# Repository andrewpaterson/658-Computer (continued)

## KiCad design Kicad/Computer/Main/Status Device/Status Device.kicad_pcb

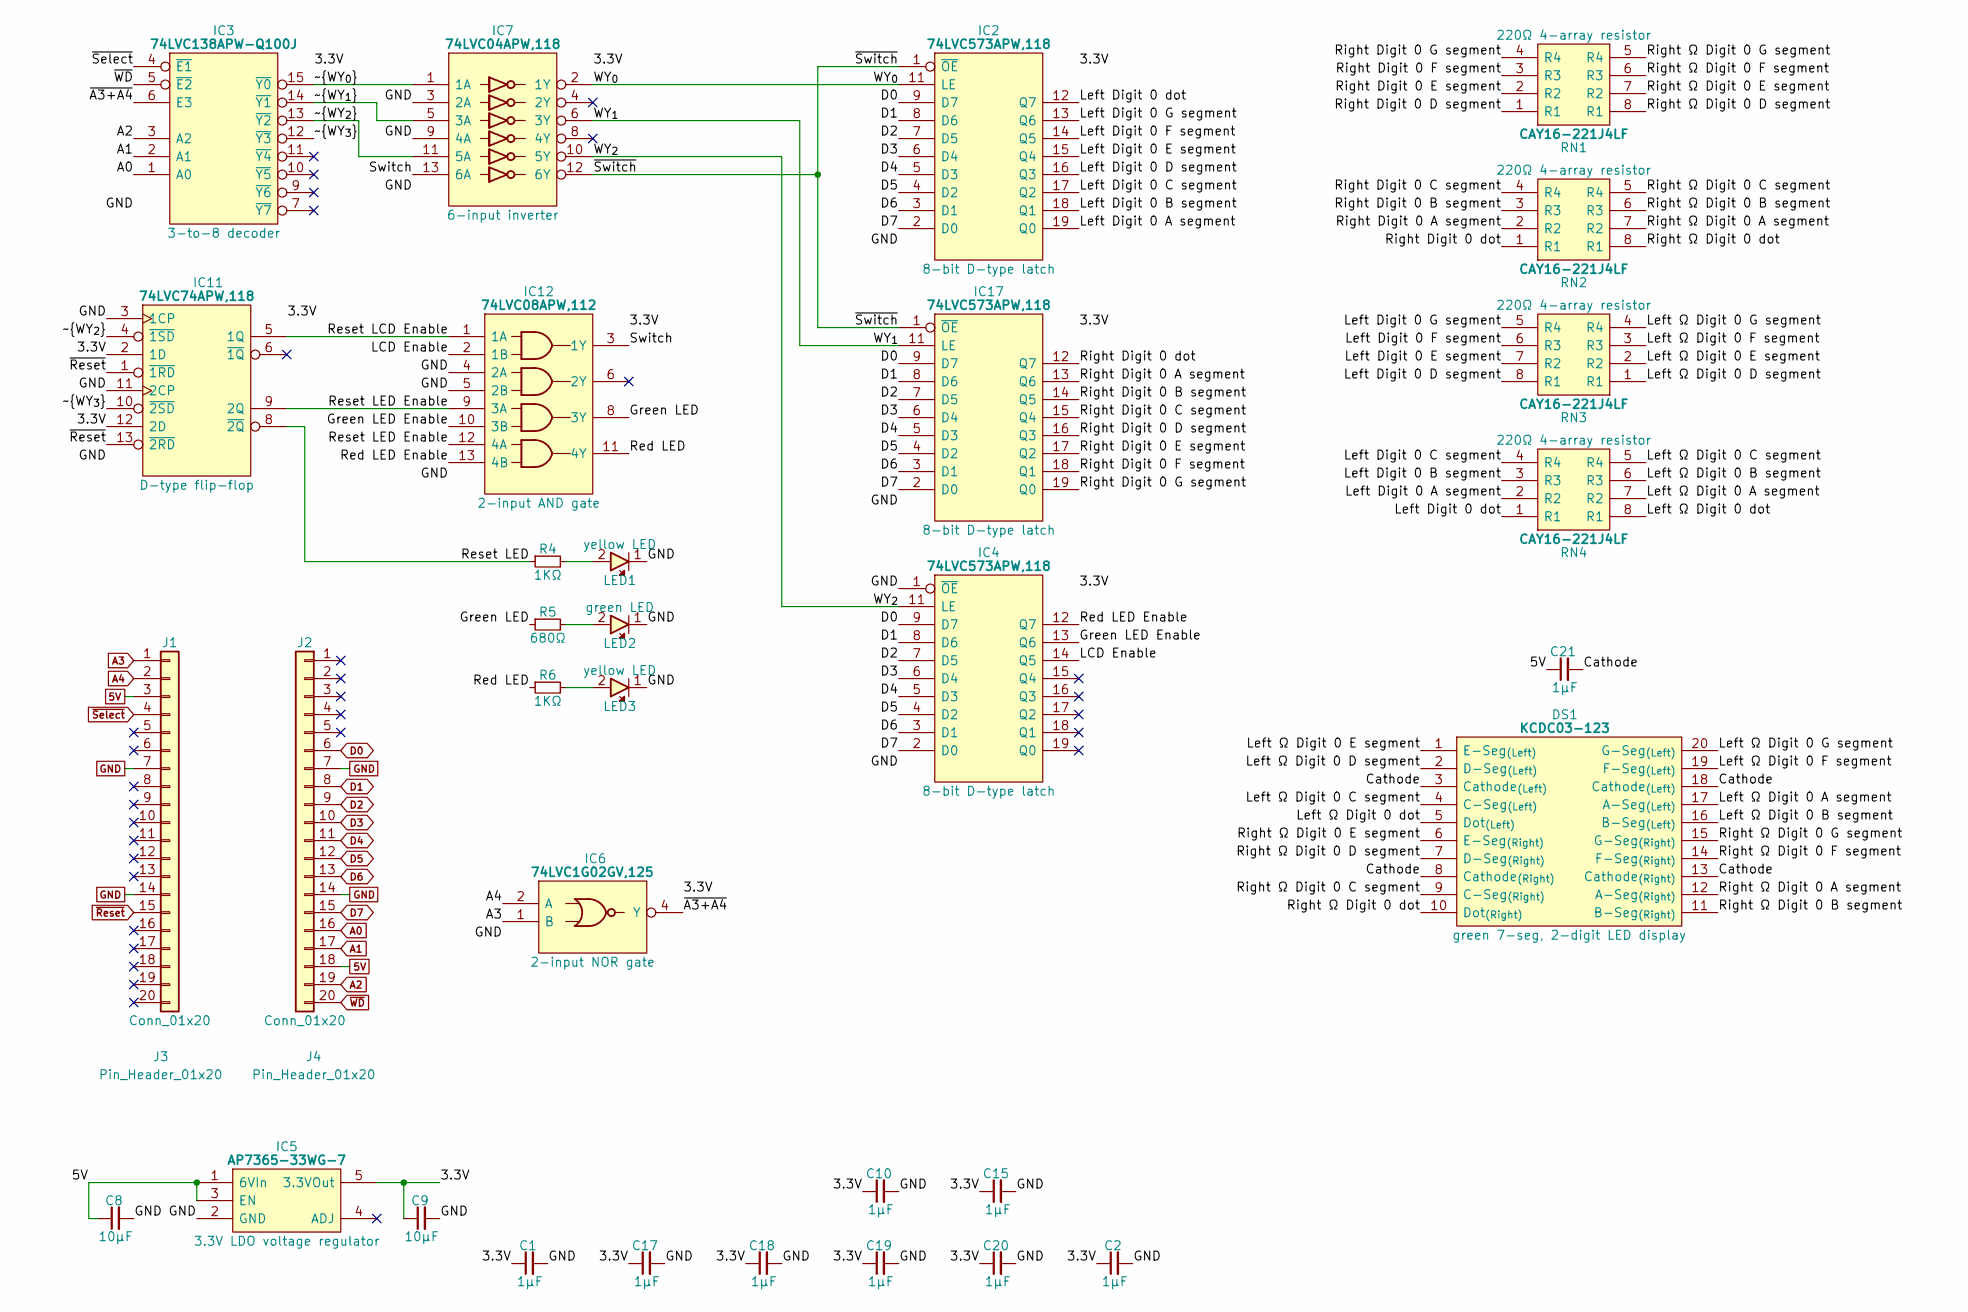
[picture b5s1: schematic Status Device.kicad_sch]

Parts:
C1, C2, C10, C15, C17, C18, C19, C20: 1μF; C_0805
C8, C9: 10µF; C_0805
C21: 1µF; C_0805
DS1: KCDC03-123; KCDC03123; Manufacturer_Part_Number KCDC03-123; Mouser Part Number N/A
IC2, IC4, IC17: 74LVC573APW,118; SOP65P640X110-20N; Mouser Part Number 771-74LVC573APW-T
IC3: 74LVC138APW-Q100J; SOP65P640X110-16N; Mouser Part Number 771-74LVC138APWQ100J
IC5: AP7365-33WG-7; SOT95P285X130-5N; Manufacturer_Part_Number AP7365-33WG-7; Mouser Part Number 621-AP7365-33WG-7
IC6: 74LVC1G02GV,125; SOT95P275X110-5N; Manufacturer_Part_Number 74LVC1G02GV,125; Mouser Part Number 771-LVC1G02GV125
IC7: 74LVC04APW,118; SOP65P640X110-14N; Manufacturer_Part_Number 74LVC04APW,118; Mouser Part Number 771-74LVC04APW-T
IC11: 74LVC74APW,118; SOP65P640X110-14N; Mouser Part Number 771-74LVC74APW-T
IC12: 74LVC08APW,112; SOP65P640X110-14N; Manufacturer_Part_Number 74LVC08APW,112; Mouser Part Number 771-74LVC08APW
J1, J2: Conn_01x20; SIP_20_Pins
J3, J4: Pin_Header_01x20; PinHeader_1x20_P2.54mm_Vertical
LED1, LED3: 150224YS73100A; 150224BS73100A
LED2: 150224VS73100A; Manufacturer_Part_Number 150224VS73100A; Mouser Part Number 710-150224VS73100A
R4, R6: 1KΩ; R_0805
R5: 680Ω; R_0805
RN1, RN2, RN3, RN4: CAY16-221J4LF; CAY16-F4; Manufacturer_Part_Number CAY16-221J4LF; Mouser Part Number 652-CAY16-221J4LF

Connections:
5V: C8.1, C21.1, IC5.1 (6VIn), IC5.3 (EN), J1.3, J2.18
/3.3V: C1.1, C2.1, C9.1, C10.1, C15.1, C17.1, C18.1, C19.1, C20.1, IC2.20 (3V), IC3.16 (3V), IC4.20 (3V), IC5.5 (3.3VOut), IC6.5 (3V), IC7.14 (3V), IC11.2 (1D), IC11.12 (2D), IC11.14 (3V), IC12.14 (3V), IC17.20 (3V)
/Cathode: C21.2, DS1.3 (Cathode_{(Left)}), DS1.8 (Cathode_{(Right)}), DS1.13 (Cathode_{(Right)}), DS1.18 (Cathode_{(Left)})
/Green LED: IC12.8 (3Y), R5.1
/Green LED Enable: IC4.13 (Q6), IC12.10 (3B)
/LCD Enable: IC4.14 (Q5), IC12.2 (1B)
/Left Digit 0 A segment: IC2.19 (Q0), RN4.2 (R2)
/Left Digit 0 B segment: IC2.18 (Q1), RN4.3 (R3)
/Left Digit 0 C segment: IC2.17 (Q2), RN4.4 (R4)
/Left Digit 0 D segment: IC2.16 (Q3), RN3.8 (R1)
/Left Digit 0 E segment: IC2.15 (Q4), RN3.7 (R2)
/Left Digit 0 F segment: IC2.14 (Q5), RN3.6 (R3)
/Left Digit 0 G segment: IC2.13 (Q6), RN3.5 (R4)
/Left Digit 0 dot: IC2.12 (Q7), RN4.1 (R1)
/Left Ω Digit 0 A segment: DS1.17 (A-Seg_{(Left)}), RN4.7 (R2)
/Left Ω Digit 0 B segment: DS1.16 (B-Seg_{(Left)}), RN4.6 (R3)
/Left Ω Digit 0 C segment: DS1.4 (C-Seg_{(Left)}), RN4.5 (R4)
/Left Ω Digit 0 D segment: DS1.2 (D-Seg_{(Left)}), RN3.1 (R1)
/Left Ω Digit 0 E segment: DS1.1 (E-Seg_{(Left)}), RN3.2 (R2)
/Left Ω Digit 0 F segment: DS1.19 (F-Seg_{(Left)}), RN3.3 (R3)
/Left Ω Digit 0 G segment: DS1.20 (G-Seg_{(Left)}), RN3.4 (R4)
/Left Ω Digit 0 dot: DS1.5 (Dot_{(Left)}), RN4.8 (R1)
/Red LED: IC12.11 (4Y), R6.1
/Red LED Enable: IC4.12 (Q7), IC12.13 (4B)
/Reset LCD Enable: IC11.5 (1Q), IC12.1 (1A)
/Reset LED: IC11.8 (~2Q), R4.1
/Reset LED Enable: IC11.9 (2Q), IC12.9 (3A), IC12.12 (4A)
/Right Digit 0 A segment: IC17.13 (Q6), RN2.2 (R2)
/Right Digit 0 B segment: IC17.14 (Q5), RN2.3 (R3)
/Right Digit 0 C segment: IC17.15 (Q4), RN2.4 (R4)
/Right Digit 0 D segment: IC17.16 (Q3), RN1.1 (R1)
/Right Digit 0 E segment: IC17.17 (Q2), RN1.2 (R2)
/Right Digit 0 F segment: IC17.18 (Q1), RN1.3 (R3)
/Right Digit 0 G segment: IC17.19 (Q0), RN1.4 (R4)
/Right Digit 0 dot: IC17.12 (Q7), RN2.1 (R1)
/Right Ω Digit 0 A segment: DS1.12 (A-Seg_{(Right)}), RN2.7 (R2)
/Right Ω Digit 0 B segment: DS1.11 (B-Seg_{(Right)}), RN2.6 (R3)
/Right Ω Digit 0 C segment: DS1.9 (C-Seg_{(Right)}), RN2.5 (R4)
/Right Ω Digit 0 D segment: DS1.7 (D-Seg_{(Right)}), RN1.8 (R1)
/Right Ω Digit 0 E segment: DS1.6 (E-Seg_{(Right)}), RN1.7 (R2)
/Right Ω Digit 0 F segment: DS1.14 (F-Seg_{(Right)}), RN1.6 (R3)
/Right Ω Digit 0 G segment: DS1.15 (G-Seg_{(Right)}), RN1.5 (R4)
/Right Ω Digit 0 dot: DS1.10 (Dot_{(Right)}), RN2.8 (R1)
/Switch: IC7.13 (6A), IC12.3 (1Y)
/WY_{0}: IC2.11 (LE), IC7.2 (1Y)
/WY_{1}: IC7.6 (3Y), IC17.11 (LE)
/WY_{2}: IC4.11 (LE), IC7.10 (5Y)
/~A3+A4: IC3.6 (E3), IC6.4 (Y)
/~Switch: IC2.1 (~OE), IC7.12 (6Y), IC17.1 (~OE)
/~WY_{0}: IC3.15 (~Y0), IC7.1 (1A)
/~WY_{1}: IC3.14 (~Y1), IC7.5 (3A)
/~WY_{2}: IC3.13 (~Y2), IC7.11 (5A), IC11.4 (~1SD)
/~WY_{3}: IC3.12 (~Y3), IC11.10 (~2SD)
A0: IC3.1 (A0), J2.16
A1: IC3.2 (A1), J2.17
A2: IC3.3 (A2), J2.19
A3: IC6.1 (B), J1.1
A4: IC6.2 (A), J1.2
D0: IC2.9 (D7), IC4.9 (D7), IC17.9 (D7), J2.6
D1: IC2.8 (D6), IC4.8 (D6), IC17.8 (D6), J2.8
D2: IC2.7 (D5), IC4.7 (D5), IC17.7 (D5), J2.9
D3: IC2.6 (D4), IC4.6 (D4), IC17.6 (D4), J2.10
D4: IC2.5 (D3), IC4.5 (D3), IC17.5 (D3), J2.11
D5: IC2.4 (D2), IC4.4 (D2), IC17.4 (D2), J2.12
D6: IC2.3 (D1), IC4.3 (D1), IC17.3 (D1), J2.13
D7: IC2.2 (D0), IC4.2 (D0), IC17.2 (D0), J2.15
GND: C1.2, C2.2, C8.2, C9.2, C10.2, C15.2, C17.2, C18.2, C19.2, C20.2, IC2.10 (GND), IC3.8 (GND), IC4.1 (~OE), IC4.10 (GND), IC5.2 (GND), IC6.3 (GND), IC7.3 (2A), IC7.7 (GND), IC7.9 (4A), IC11.3 (1CP), IC11.7 (GND), IC11.11 (2CP), IC12.4 (2A), IC12.5 (2B), IC12.7 (GND), IC17.10 (GND), J1.7, J1.14, J2.7, J2.14, LED1.1, LED2.1, LED3.1
unnamed: LED1.2, R4.2
unnamed: LED2.2, R5.2
unnamed: LED3.2, R6.2
~Reset: IC11.1 (~1RD), IC11.13 (~2RD), J1.15
~Select: IC3.4 (~E1), J1.4
~WD: IC3.5 (~E2), J2.20

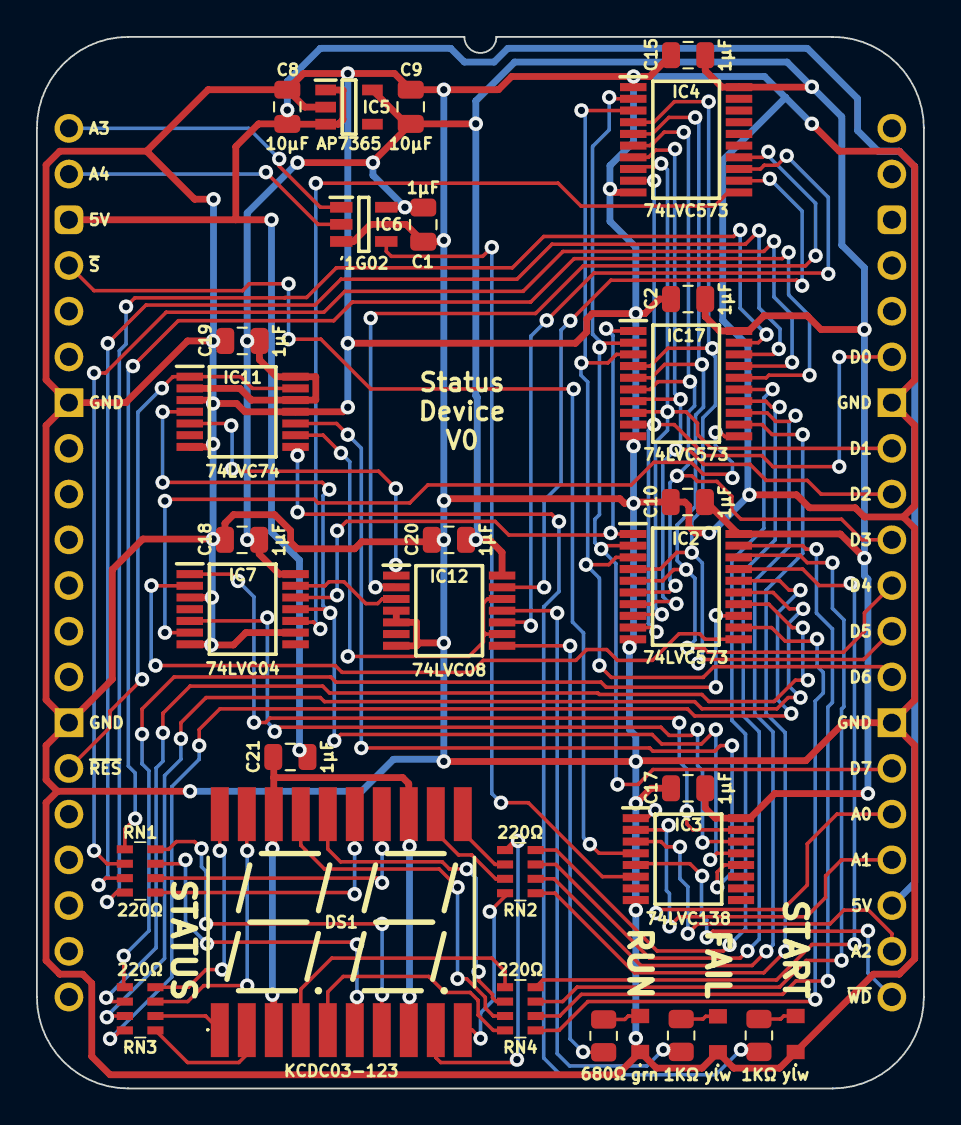
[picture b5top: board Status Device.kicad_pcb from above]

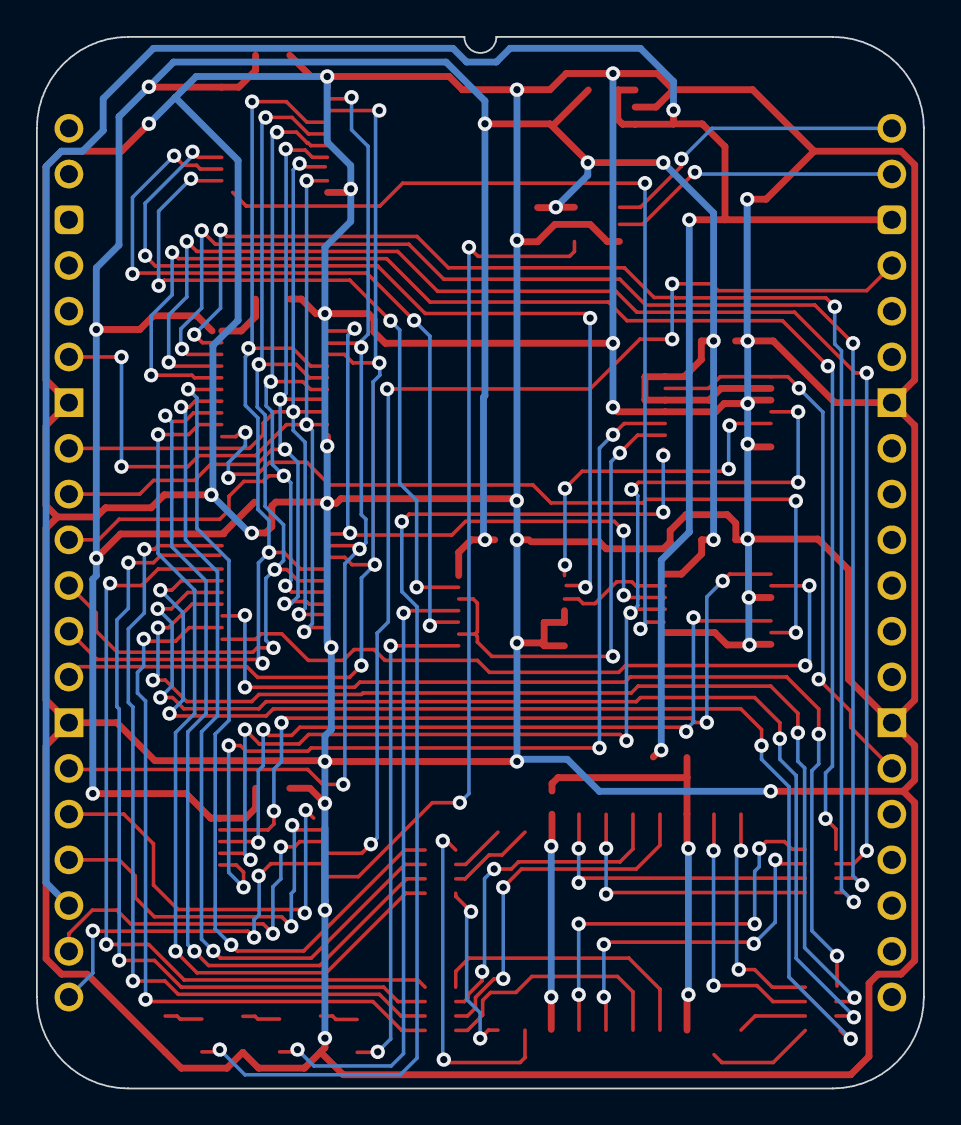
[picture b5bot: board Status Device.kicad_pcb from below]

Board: 2 copper layers, 49.3 x 58.4 mm, 35 parts (2 on the bottom side), 73 nets.

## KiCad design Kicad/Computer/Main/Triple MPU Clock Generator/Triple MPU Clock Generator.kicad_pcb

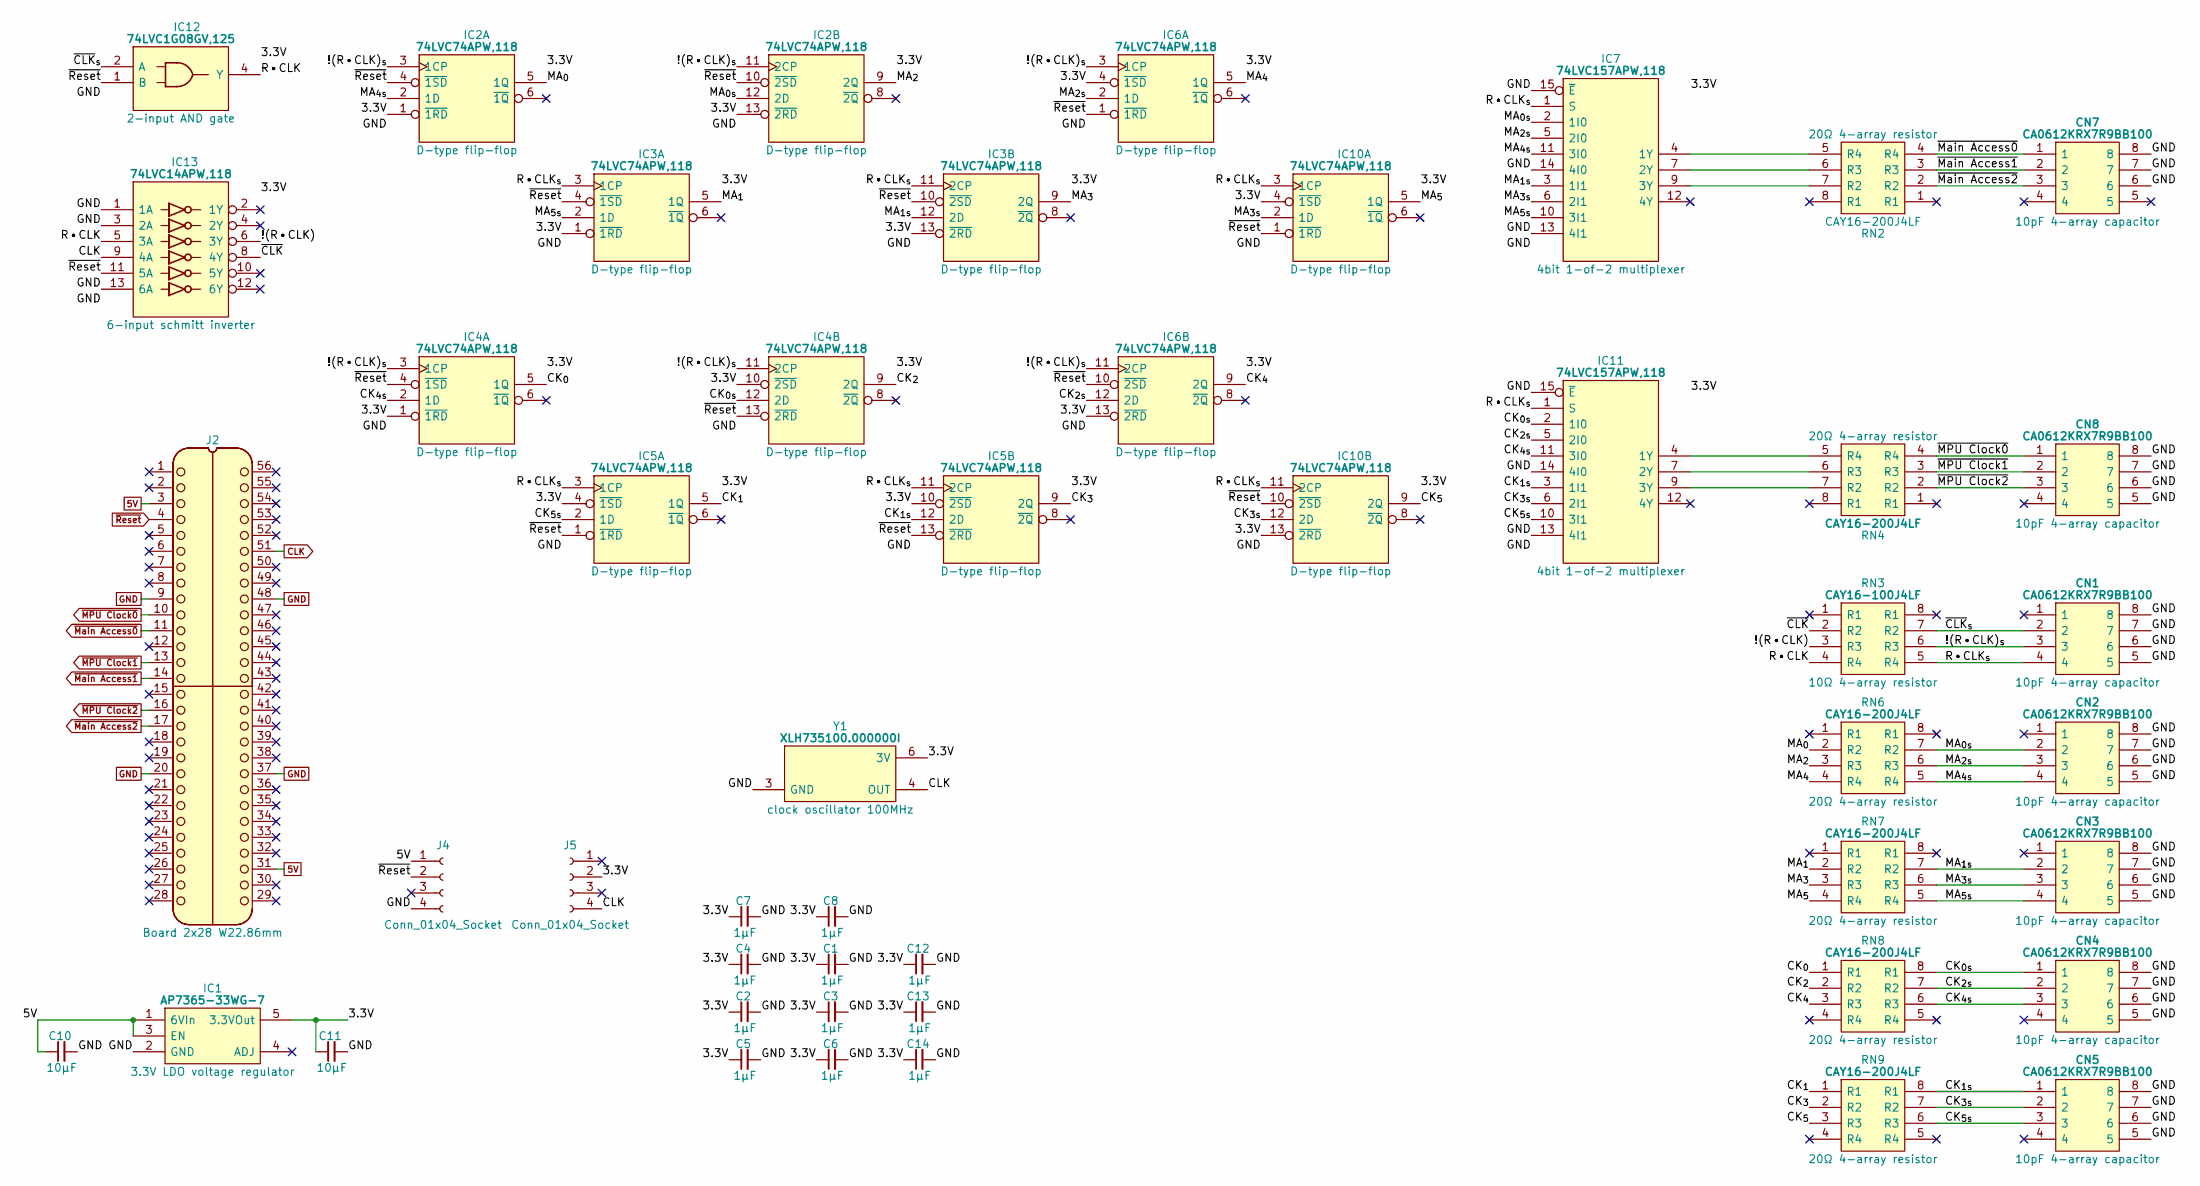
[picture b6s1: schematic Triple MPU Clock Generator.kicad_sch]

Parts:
C1, C2, C3, C4, C5, C6, C7, C8, C12, C13, C14: 1μF; C_0805
C10, C11: 10µF; C_0805
CN1, CN2, CN3, CN4, CN5, CN7, CN8: CA0612KRX7R9BB100; Manufacturer_Part_Number CA0612KRX7R9BB102; Mouser Part Number 603-CA612KRX7R9BB102
IC1: AP7365-33WG-7; SOT95P285X130-5N; Manufacturer_Part_Number AP7365-33WG-7; Mouser Part Number 621-AP7365-33WG-7
IC2, IC3, IC4, IC5, IC6, IC10: 74LVC74APW,118; SOP65P640X110-14N; Mouser Part Number 771-74LVC74APW-T
IC7, IC11: 74LVC157APW,118; SOP65P640X110-16N; Mouser Part Number 771-74LVC157APW-T
IC12: 74LVC1G08GV,125; SOT95P275X110-5N; Manufacturer_Part_Number 74LVC1G08GV,125; Mouser Part Number 771-74LVC1G08GV
IC13: 74LVC14APW,118; SOP65P640X110-14N; Manufacturer_Part_Number 74LVC14APW,118; Mouser Part Number 771-74LVC14APW-T
J2: Board 2x28 W22.86mm; DIP-56_Board_W22.86mm
J4, J5: Conn_01x04_Socket; PinSocket_1x04_P2.54mm_Vertical
RN2, RN4, RN6, RN7, RN8, RN9: CAY16-200J4LF; CAY16-F4; Manufacturer_Part_Number CAY16-331J4LF; Mouser Part Number 652-CAY16-331J4LF
RN3: CAY16-100J4LF; CAY16-F4; Manufacturer_Part_Number CAY16-331J4LF; Mouser Part Number 652-CAY16-331J4LF
Y1: XLH735100.000000I; XLH735100000000I; Mouser Part Number 972-XLH735100000000I

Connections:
5V: C10.1, IC1.1 (6VIn), IC1.3 (EN), J2.3, J2.31, J4.1
/3.3V: C1.1, C2.1, C3.1, C4.1, C5.1, C6.1, C7.1, C8.1, C11.1, C12.1, C13.1, C14.1, IC1.5 (3.3VOut), IC2.1 (~1RD), IC2.13 (~2RD), IC2.14 (3V), IC3.1 (~1RD), IC3.13 (~2RD), IC3.14 (3V), IC4.1 (~1RD), IC4.10 (~2SD), IC4.14 (3V), IC5.4 (~1SD), IC5.10 (~2SD), IC5.14 (3V), IC6.4 (~1SD), IC6.13 (~2RD), IC6.14 (3V), IC7.16 (3V), IC10.4 (~1SD), IC10.13 (~2RD), IC10.14 (3V), IC11.16 (3V), IC12.5 (3V), IC13.14 (3V), J5.2, Y1.6 (3V); also elsewhere on the board
/!(R•CLK): IC13.6 (3Y), RN3.3 (R3)
/!(R•CLK)_{s}: CN1.3, IC2.3 (1CP), IC2.11 (2CP), IC4.3 (1CP), IC4.11 (2CP), IC6.3 (1CP), IC6.11 (2CP), RN3.6 (R3)
/CK_{0s}: CN4.1, IC4.12 (2D), IC11.2 (1I0), RN8.8 (R1)
/CK_{0}: IC4.5 (1Q), RN8.1 (R1)
/CK_{1s}: CN5.1, IC5.12 (2D), IC11.3 (1I1), RN9.8 (R1)
/CK_{1}: IC5.5 (1Q), RN9.1 (R1)
/CK_{2s}: CN4.2, IC6.12 (2D), IC11.5 (2I0), RN8.7 (R2)
/CK_{2}: IC4.9 (2Q), RN8.2 (R2)
/CK_{3s}: CN5.2, IC10.12 (2D), IC11.6 (2I1), RN9.7 (R2)
/CK_{3}: IC5.9 (2Q), RN9.2 (R2)
/CK_{4s}: CN4.3, IC4.2 (1D), IC11.11 (3I0), RN8.6 (R3)
/CK_{4}: IC6.9 (2Q), RN8.3 (R3)
/CK_{5s}: CN5.3, IC5.2 (1D), IC11.10 (3I1), RN9.6 (R3)
/CK_{5}: IC10.9 (2Q), RN9.3 (R3)
/MA_{0s}: CN2.2, IC2.12 (2D), IC7.2 (1I0), RN6.7 (R2)
/MA_{0}: IC2.5 (1Q), RN6.2 (R2)
/MA_{1s}: CN3.2, IC3.12 (2D), IC7.3 (1I1), RN7.7 (R2)
/MA_{1}: IC3.5 (1Q), RN7.2 (R2)
/MA_{2s}: CN2.3, IC6.2 (1D), IC7.5 (2I0), RN6.6 (R3)
/MA_{2}: IC2.9 (2Q), RN6.3 (R3)
/MA_{3s}: CN3.3, IC7.6 (2I1), IC10.2 (1D), RN7.6 (R3)
/MA_{3}: IC3.9 (2Q), RN7.3 (R3)
/MA_{4s}: CN2.4, IC2.2 (1D), IC7.11 (3I0), RN6.5 (R4)
/MA_{4}: IC6.5 (1Q), RN6.4 (R4)
/MA_{5s}: CN3.4, IC3.2 (1D), IC7.10 (3I1), RN7.5 (R4)
/MA_{5}: IC10.5 (1Q), RN7.4 (R4)
/R•CLK: IC12.4 (Y), IC13.5 (3A), RN3.4 (R4)
/R•CLK_{s}: CN1.4, IC3.3 (1CP), IC3.11 (2CP), IC5.3 (1CP), IC5.11 (2CP), IC7.1 (S), IC10.3 (1CP), IC10.11 (2CP), IC11.1 (S), RN3.5 (R4)
/~CLK: IC13.8 (4Y), RN3.2 (R2)
/~CLK_{s}: CN1.2, IC12.2 (A), RN3.7 (R2)
CLK: IC13.9 (4A), J2.51, J5.4, Y1.4 (OUT)
GND: C1.2, C2.2, C3.2, C4.2, C5.2, C6.2, C7.2, C8.2, C10.2, C11.2, C12.2, C13.2, C14.2, CN1.5, CN1.6, CN1.7, CN1.8, CN2.5, CN2.6, CN2.7, CN2.8, CN3.5, CN3.6, CN3.7, CN3.8, CN4.5, CN4.6, CN4.7, CN4.8, CN5.5, CN5.6, CN5.7, CN5.8, CN7.6, CN7.7, CN7.8, CN8.5, CN8.6, CN8.7, CN8.8, IC1.2 (GND), IC2.7 (GND), IC3.7 (GND), IC4.7 (GND), IC5.7 (GND), IC6.7 (GND), IC7.8 (GND), IC7.13 (4I1), IC7.14 (4I0), IC7.15 (~E), IC10.7 (GND), IC11.8 (GND), IC11.13 (4I1), IC11.14 (4I0), IC11.15 (~E), IC12.3 (GND), IC13.1 (1A), IC13.3 (2A), IC13.7 (GND), IC13.13 (6A), J2.9, J2.20, J2.37, J2.48, J4.4, Y1.3 (GND); also elsewhere on the board
unnamed: IC7.4 (1Y), RN2.5 (R4)
unnamed: IC7.7 (2Y), RN2.6 (R3)
unnamed: IC7.9 (3Y), RN2.7 (R2)
unnamed: IC11.4 (1Y), RN4.5 (R4)
unnamed: IC11.7 (2Y), RN4.6 (R3)
unnamed: IC11.9 (3Y), RN4.7 (R2)
WATCH CLK: J2.55; also elsewhere on the board
~MPU Clock0: CN8.1, J2.10, RN4.4 (R4)
~MPU Clock1: CN8.2, J2.13, RN4.3 (R3)
~MPU Clock2: CN8.3, J2.16, RN4.2 (R2)
~Main Access0: CN7.1, J2.11, RN2.4 (R4)
~Main Access1: CN7.2, J2.14, RN2.3 (R3)
~Main Access2: CN7.3, J2.17, RN2.2 (R2)
~Reset: IC2.4 (~1SD), IC2.10 (~2SD), IC3.4 (~1SD), IC3.10 (~2SD), IC4.4 (~1SD), IC4.13 (~2RD), IC5.1 (~1RD), IC5.13 (~2RD), IC6.1 (~1RD), IC6.10 (~2SD), IC10.1 (~1RD), IC10.10 (~2SD), IC12.1 (B), IC13.11 (5A), J2.4, J4.2

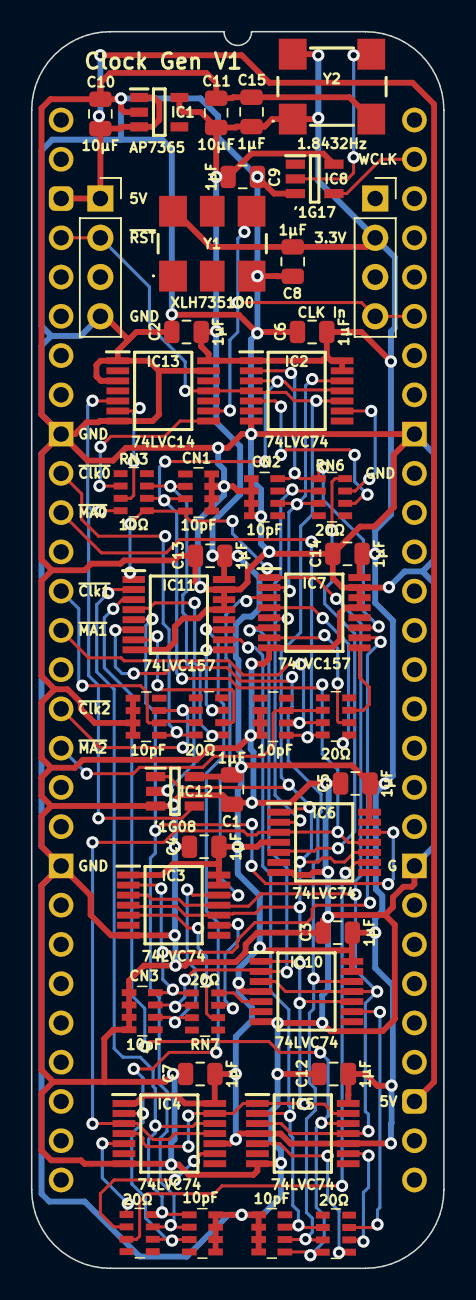
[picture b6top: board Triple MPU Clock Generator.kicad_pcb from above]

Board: 2 copper layers, 26.7 x 80.0 mm, 46 parts (0 on the bottom side), 49 nets.

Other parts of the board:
C9, C15: 1μF; C_0805
IC8: 74LVC1G17GV,125; SOT95P275X110-5N
Y2: LFSPXO020733

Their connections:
/3.3V: C9.1, C15.1, IC8.5 (3V), Y2.1 (EN), Y2.4 (3V); also elsewhere on the board
GND: C9.2, C15.2, IC8.3 (GND), Y2.2 (GND); also elsewhere on the board
unnamed: IC8.2 (A), Y2.3 (OUT)
WATCH CLK: IC8.4 (Y); also elsewhere on the board

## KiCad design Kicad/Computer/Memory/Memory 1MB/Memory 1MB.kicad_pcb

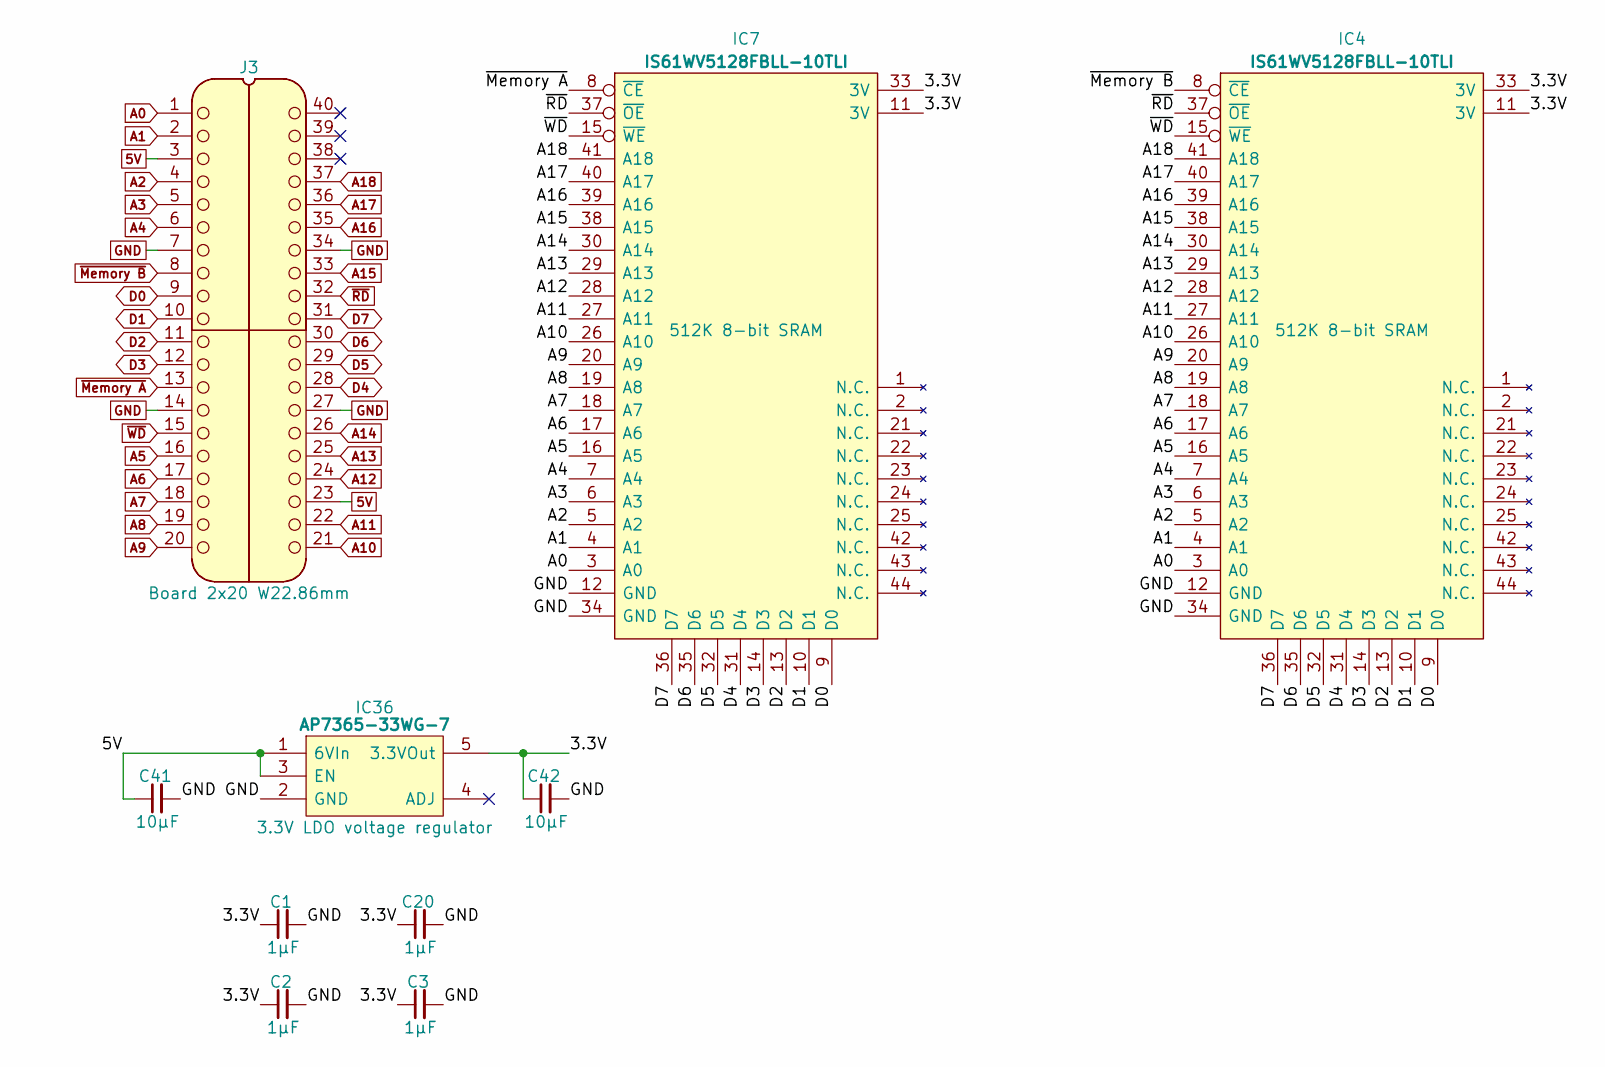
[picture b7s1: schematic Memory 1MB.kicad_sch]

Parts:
C1, C2, C3, C20: 1μF; C_0805
C41, C42: 10μF; C_0805
IC4, IC7: IS61WV5128FBLL-10TLI; SOP80P1176X120-44N; Manufacturer_Part_Number IS61WV5128FBLL-10TLI
IC36: AP7365-33WG-7; SOT95P285X130-5N; Manufacturer_Part_Number AP7365-33WG-7; Mouser Part Number 621-AP7365-33WG-7
J3: Board 2x20 W22.86mm; DIP-40_Board_W22.86mm

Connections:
5V: C41.1, IC36.1 (6VIn), IC36.3 (EN), J3.3, J3.23
/3.3V: C1.1, C2.1, C3.1, C20.1, C42.1, IC4.11 (3V), IC4.33 (3V), IC7.11 (3V), IC7.33 (3V), IC36.5 (3.3VOut)
A0: IC4.3 (A0), IC7.3 (A0), J3.1
A1: IC4.4 (A1), IC7.4 (A1), J3.2
A2: IC4.5 (A2), IC7.5 (A2), J3.4
A3: IC4.6 (A3), IC7.6 (A3), J3.5
A4: IC4.7 (A4), IC7.7 (A4), J3.6
A5: IC4.16 (A5), IC7.16 (A5), J3.16
A6: IC4.17 (A6), IC7.17 (A6), J3.17
A7: IC4.18 (A7), IC7.18 (A7), J3.18
A8: IC4.19 (A8), IC7.19 (A8), J3.19
A9: IC4.20 (A9), IC7.20 (A9), J3.20
A10: IC4.26 (A10), IC7.26 (A10), J3.21
A11: IC4.27 (A11), IC7.27 (A11), J3.22
A12: IC4.28 (A12), IC7.28 (A12), J3.24
A13: IC4.29 (A13), IC7.29 (A13), J3.25
A14: IC4.30 (A14), IC7.30 (A14), J3.26
A15: IC4.38 (A15), IC7.38 (A15), J3.33
A16: IC4.39 (A16), IC7.39 (A16), J3.35
A17: IC4.40 (A17), IC7.40 (A17), J3.36
A18: IC4.41 (A18), IC7.41 (A18), J3.37
D0: IC4.9 (D0), IC7.9 (D0), J3.9
D1: IC4.10 (D1), IC7.10 (D1), J3.10
D2: IC4.13 (D2), IC7.13 (D2), J3.11
D3: IC4.14 (D3), IC7.14 (D3), J3.12
D4: IC4.31 (D4), IC7.31 (D4), J3.28
D5: IC4.32 (D5), IC7.32 (D5), J3.29
D6: IC4.35 (D6), IC7.35 (D6), J3.30
D7: IC4.36 (D7), IC7.36 (D7), J3.31
GND: C1.2, C2.2, C3.2, C20.2, C41.2, C42.2, IC4.12 (GND), IC4.34 (GND), IC7.12 (GND), IC7.34 (GND), IC36.2 (GND), J3.7, J3.14, J3.27, J3.34
~Memory A: IC7.8 (~CE), J3.13
~Memory B: IC4.8 (~CE), J3.8
~RD: IC4.37 (~OE), IC7.37 (~OE), J3.32
~WD: IC4.15 (~WE), IC7.15 (~WE), J3.15

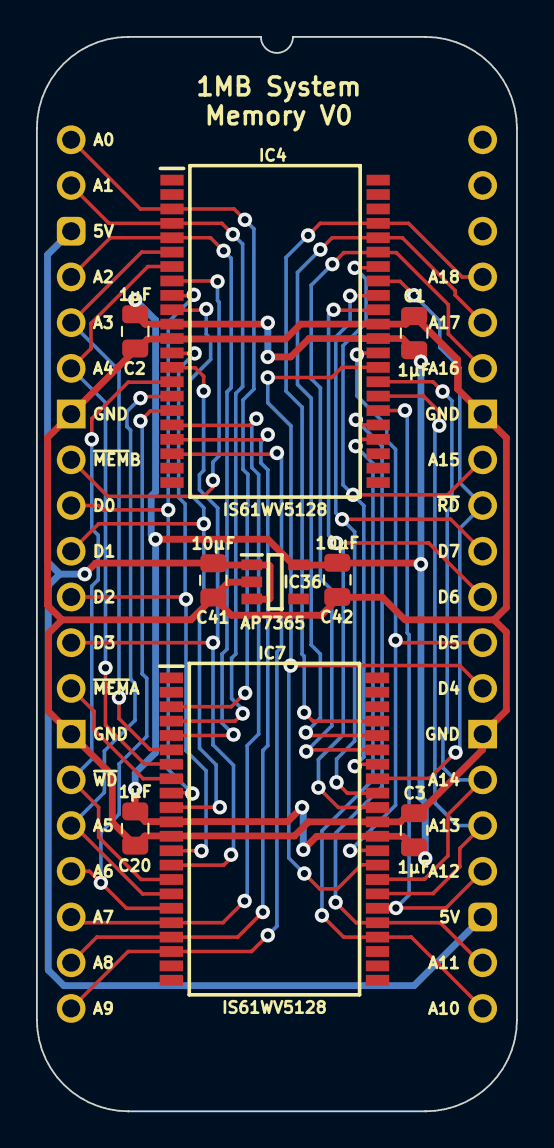
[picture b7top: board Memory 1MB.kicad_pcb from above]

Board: 2 copper layers, 26.7 x 59.7 mm, 10 parts (0 on the bottom side), 34 nets.

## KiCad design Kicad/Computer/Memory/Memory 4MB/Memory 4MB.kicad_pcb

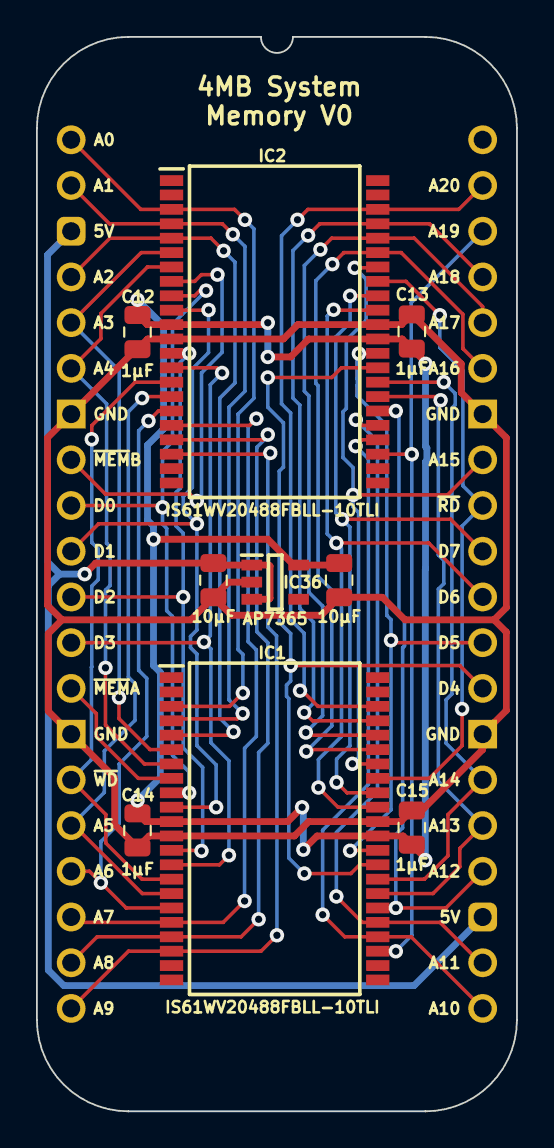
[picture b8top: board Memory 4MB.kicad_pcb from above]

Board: 2 copper layers, 26.7 x 59.7 mm, 10 parts (0 on the bottom side), 36 nets.

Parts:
C12, C13, C14, C15: 1µF; C_0805
C41, C42: 10μF; C_0805
IC1, IC2: IS61WV20488FBLL-10TLI; SOP80P1176X120-44N
IC36: AP7365-33WG-7; SOT95P285X130-5N
J7: Board 2x20 W22.86mm; DIP-40_Board_W22.86mm

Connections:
5V: C41.1, IC36.1 (6VIn), IC36.3 (EN), J7.3, J7.23
/3.3V: C12.1, C13.1, C14.1, C15.1, C42.1, IC1.11 (3V), IC1.33 (3V), IC2.11 (3V), IC2.33 (3V), IC36.5 (3.3VOut)
A0: IC1.3 (A0), IC2.3 (A0), J7.1
A1: IC1.4 (A1), IC2.4 (A1), J7.2
A2: IC1.5 (A2), IC2.5 (A2), J7.4
A3: IC1.6 (A3), IC2.6 (A3), J7.5
A4: IC1.7 (A4), IC2.7 (A4), J7.6
A5: IC1.16 (A5), IC2.16 (A5), J7.16
A6: IC1.17 (A6), IC2.17 (A6), J7.17
A7: IC1.18 (A7), IC2.18 (A7), J7.18
A8: IC1.19 (A8), IC2.19 (A8), J7.19
A9: IC1.20 (A9), IC2.20 (A9), J7.20
A10: IC1.26 (A10), IC2.26 (A10), J7.21
A11: IC1.27 (A11), IC2.27 (A11), J7.22
A12: IC1.28 (A12), IC2.28 (A12), J7.24
A13: IC1.29 (A13), IC2.29 (A13), J7.25
A14: IC1.30 (A14), IC2.30 (A14), J7.26
A15: IC1.38 (A15), IC2.38 (A15), J7.33
A16: IC1.39 (A16), IC2.39 (A16), J7.35
A17: IC1.40 (A17), IC2.40 (A17), J7.36
A18: IC1.41 (A18), IC2.41 (A18), J7.37
A19: IC1.25 (A19), IC2.25 (A19), J7.38
A20: IC1.42 (A20), IC2.42 (A20), J7.39
D0: IC1.9 (D0), IC2.9 (D0), J7.9
D1: IC1.10 (D1), IC2.10 (D1), J7.10
D2: IC1.13 (D2), IC2.13 (D2), J7.11
D3: IC1.14 (D3), IC2.14 (D3), J7.12
D4: IC1.31 (D4), IC2.31 (D4), J7.28
D5: IC1.32 (D5), IC2.32 (D5), J7.29
D6: IC1.35 (D6), IC2.35 (D6), J7.30
D7: IC1.36 (D7), IC2.36 (D7), J7.31
GND: C12.2, C13.2, C14.2, C15.2, C41.2, C42.2, IC1.12 (GND), IC1.34 (GND), IC2.12 (GND), IC2.34 (GND), IC36.2 (GND), J7.7, J7.14, J7.27, J7.34
~Memory A: IC1.8 (~CE), J7.13
~Memory B: IC2.8 (~CE), J7.8
~RD: IC1.37 (~OE), IC2.37 (~OE), J7.32
~WD: IC1.15 (~WE), IC2.15 (~WE), J7.15
